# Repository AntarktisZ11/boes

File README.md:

# What is this?

This is Bamses Øhlhäfvarstoppur also called Bøs.

TODO Desc. the rules of häfv.

# Why is this?

TODO

# How to build Bøs (Bamses Øhlhäfvarstoppur)

TODO

## Hardware prerequisites

[List of components](./Hardware.md)

Rough cost estimate: 1000-800kr

<details>
<summary>Pico RGB matrix pinout</summary>
<br>
TODO add pinout

</details>

### Main PCB

[Schematic PDF](./docs/pcb-boes-main/boes-schematic.pdf)

[CSV BoM](./docs/pcb-boes-main/BoM/boes-bom.csv)

[Interactive BoM](./docs/pcb-boes-main/BoM/boes-ibom.html) (Download and view in browser.)

#### Top and bottom view of PCB

### USB-C Power distribution PCB

[Schematic PDF](./docs/pcb-boes-usb-c/boes_usb-c-schematic.pdf)

[CSV BoM](./docs/pcb-boes-usb-c/BoM/boes_usb-c-bom.csv)

[Interactive BoM](./docs/pcb-boes-usb-c/BoM/boes_usb-c-ibom.html) (Download and view in browser.)

#### Top and bottom view of PCB

### Sensor PCB

[Schematic PDF](./docs/pcb-boes-sensor/boes_sensor-schematic.pdf)

[CSV BoM](./docs/pcb-boes-sensor/BoM/boes_sensor-bom.csv)

[Interactive BoM](./docs/pcb-boes-sensor/BoM/boes_sensor-ibom.html) (Download and view in browser.)

#### Top and bottom view of PCB

## Software prerequisites

The following tools and libraries are required to compile and flash the Pico.

- Arduino CLI tool (or Arduino IDE, whatever works)
- [Raspberry Pi Pico Arduino core](https://github.com/earlephilhower/arduino-pico)
- Adafruit and Arduino libraries (see below)

## Linux guide

Install Pico Arduino core (if not already prepared):

```bash
# Initialize arduino-cli
arduino-cli config init

# Add Pico url to additional_urls like this:
additional_urls: [https://github.com/earlephilhower/arduino-pico/releases/download/global/package_rp2040_index.json]

# Update index to download rp2040 config
arduino-cli core update-index

# Download Pico cores
arduino-cli core install rp2040:rp204
```

Install the required libraries:

```bash
# Note: 'arduino-cli lib install <library>' installs <library>
# and all its dependencies.

# Adafruit library required to driver the led matrix.
arduino-cli lib install "Adafruit Protomatter"

# Protothread / simulated threads in software to schedule
# timer, display and button controllers.
arduino-cli lib install "ArduinoThread"
```

## Compiling and uploading binary

After the prerequisites are satisfied you should be able to compile and upload the binary to the Pico.

```bash
# Compile and upload binary.
# (Note: For me <serial> was set to /dev/ttyACM0)
arduino-cli compile -u -p <serial> -b rp2040:rp2040:rpipicow display/display.ino
```

# Future improvements

- Separate code into thread classes (e.g. display and web server handling in their own respective class)
- Config file handling for constants/delays/logo (USB mass storage) when plugging the cable (also allow uploading configs on web server site?)
- HTML/CSS file handling (USB mass storage).. not the crude http response way that is currently implemented

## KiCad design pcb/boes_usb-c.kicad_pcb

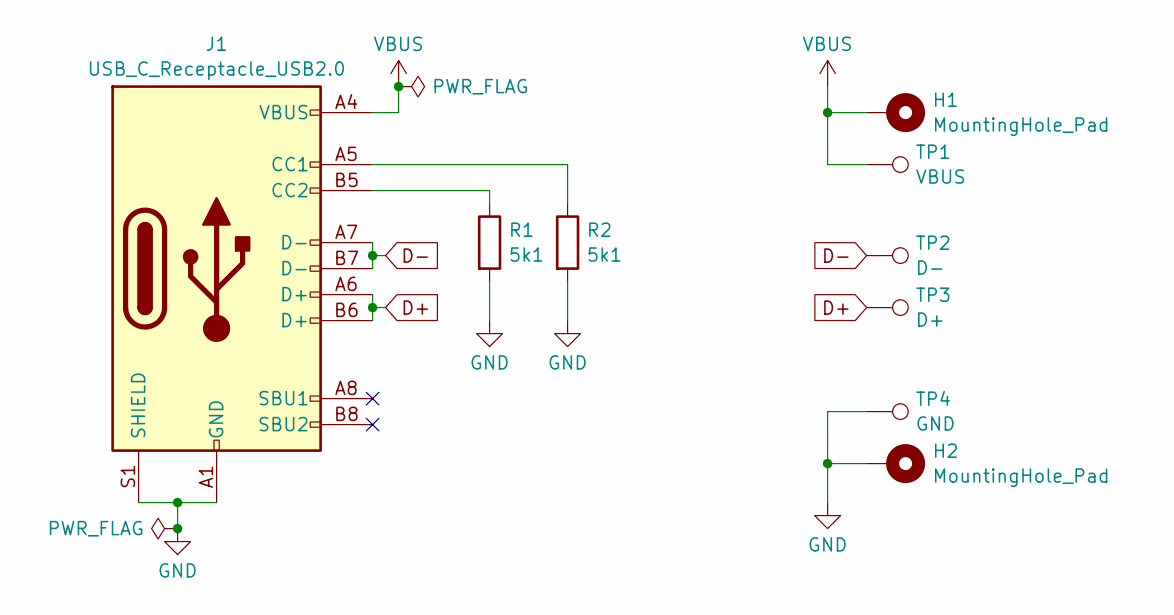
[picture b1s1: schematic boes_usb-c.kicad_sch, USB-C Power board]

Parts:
H1, H2: MountingHole_Pad; MountingHole_3.2mm_M3_Pad_TopOnly
J1: USB_C_Receptacle_USB2.0; USB_C_Receptacle_GCT_USB4105-xx-A_16P_TopMnt_Horizontal
R1, R2: 5k1; R_0603_1608Metric
TP1: VBUS; SolderWire-0.5sqmm_1x01_D0.9mm_OD2.1mm_Relief
TP2: D-; SolderWire-0.1sqmm_1x01_D0.4mm_OD1mm_Relief
TP3: D+; SolderWire-0.1sqmm_1x01_D0.4mm_OD1mm_Relief
TP4: GND; SolderWire-0.5sqmm_1x01_D0.9mm_OD2.1mm_Relief

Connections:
D+: J1.A6 (D+), J1.B6 (D+), TP3.1
D-: J1.A7 (D-), J1.B7 (D-), TP2.1
GND: H2.1, J1.A1 (GND), J1.A12 (GND), J1.B1 (GND), J1.B12 (GND), J1.S1 (SHIELD), R1.2, R2.2, TP4.1
unnamed: J1.A5 (CC1), R2.1
unnamed: J1.B5 (CC2), R1.1
VBUS: H1.1, J1.A4 (VBUS), J1.A9 (VBUS), J1.B4 (VBUS), J1.B9 (VBUS), TP1.1

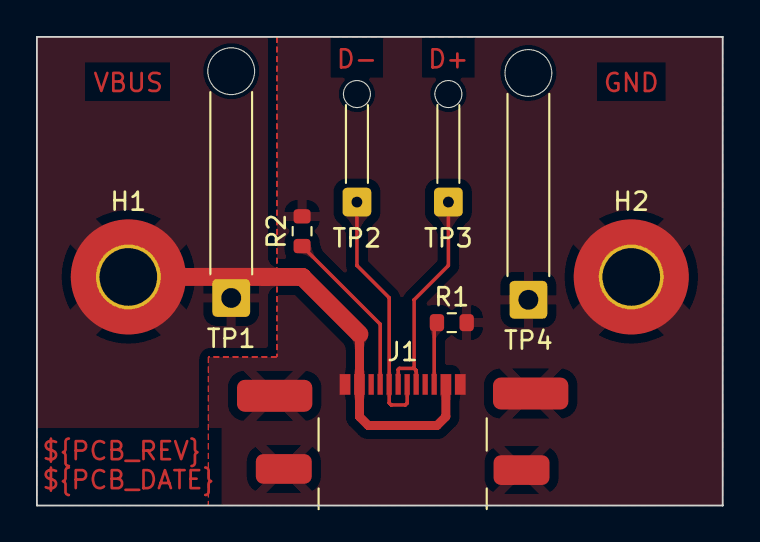
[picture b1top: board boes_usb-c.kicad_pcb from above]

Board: 2 copper layers, 38.1 x 26.0 mm, 9 parts (0 on the bottom side), 6 nets.

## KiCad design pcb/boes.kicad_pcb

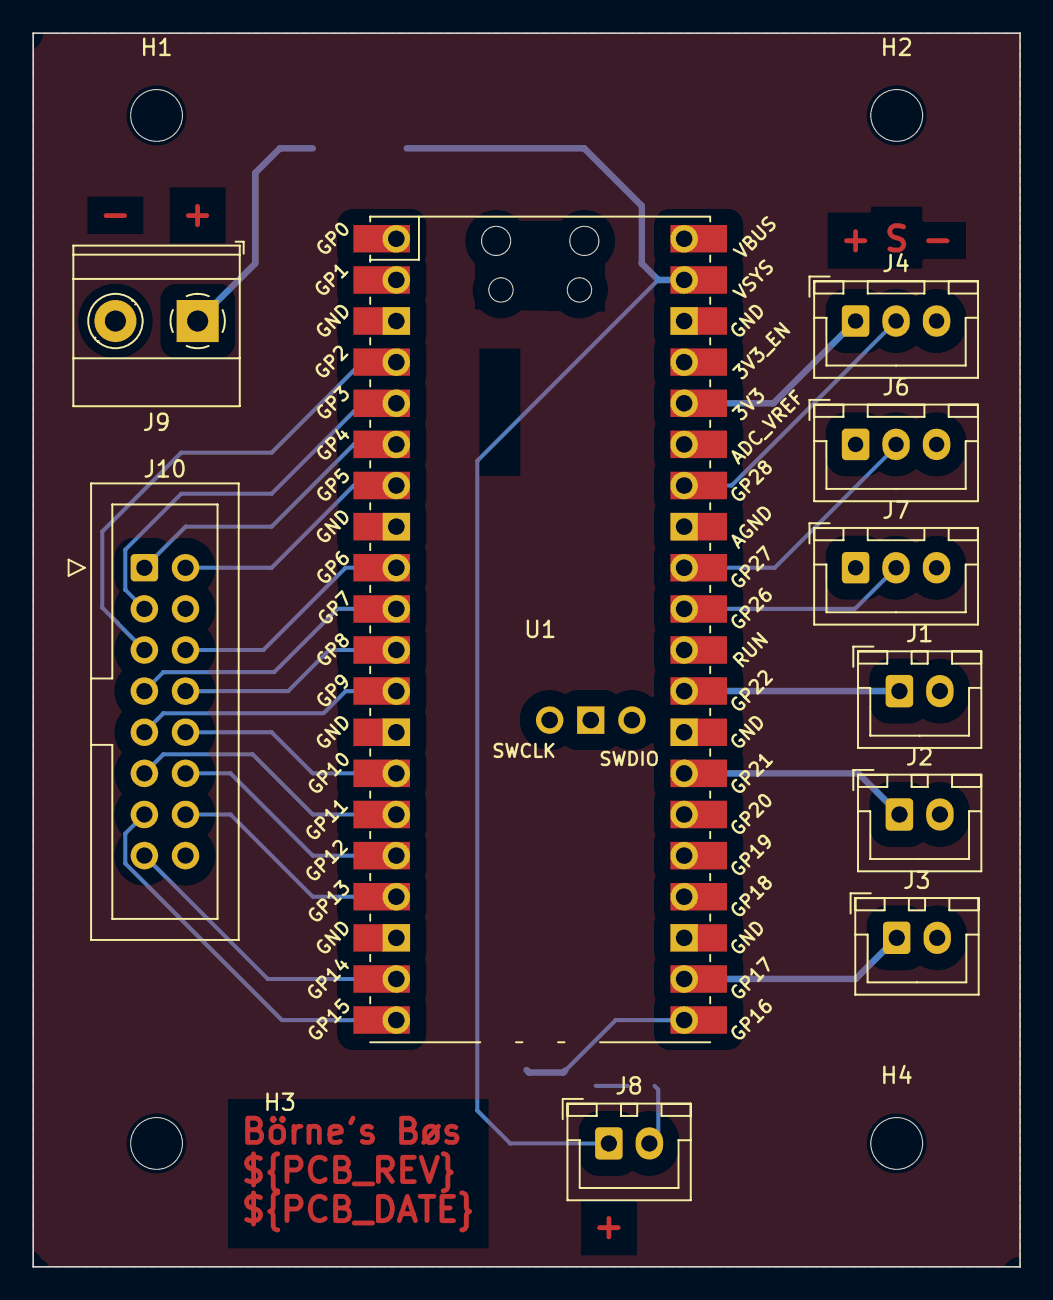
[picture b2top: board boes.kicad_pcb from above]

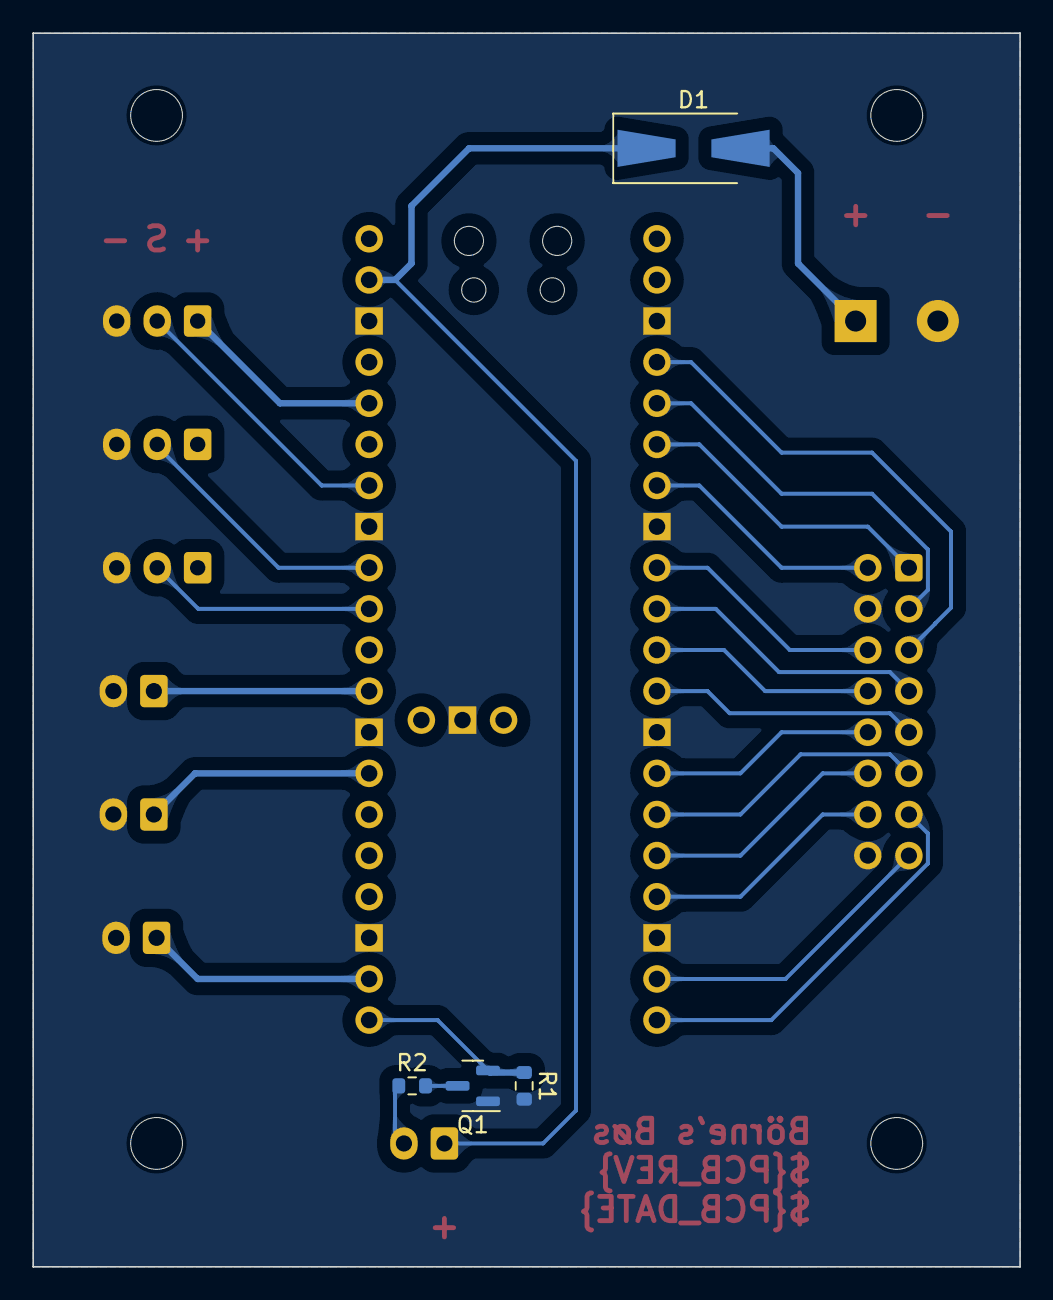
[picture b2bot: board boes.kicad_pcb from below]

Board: 2 copper layers, 61.0 x 76.2 mm, 18 parts (4 on the bottom side), 27 nets.

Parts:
D1: D_Schottky; D_SMA-SMB_Universal_Handsoldering
H1, H2, H3, H4: MountingHole; MountingHole_3.2mm_M3
J1: SW_A; JST_XH_B2B-XH-A_1x02_P2.50mm_Vertical
J2: SW_B; JST_XH_B2B-XH-A_1x02_P2.50mm_Vertical
J3: SW_C; JST_XH_B2B-XH-A_1x02_P2.50mm_Vertical
J4: Pot_J; JST_XH_B3B-XH-A_1x03_P2.50mm_Vertical
J6: Sens_J; JST_XH_B3B-XH-A_1x03_P2.50mm_Vertical
J7: Sens_P; JST_XH_B3B-XH-A_1x03_P2.50mm_Vertical
J8: Buzzer; JST_XH_B2B-XH-A_1x02_P2.50mm_Vertical
J9: +5V External; TerminalBlock_Phoenix_MKDS-1,5-2-5.08_1x02_P5.08mm_Horizont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
J10: HUB75 Display ctrl; IDC-Header_2x08_P2.54mm_Vertical
Q1: 2N7000; SOT-23
R1: 10k; R_0603_1608Metric
R2: R; R_0603_1608Metric
U1: PicoW; RPi_PicoW_SMD_TH

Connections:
+3V3: J4.1, J6.1, J7.1, U1.36 (3V3)
A: J10.9, U1.12 (GPIO9)
B: J10.10, U1.14 (GPIO10)
B1: J10.3, U1.5 (GPIO3)
B2: J10.7, U1.10 (GPIO7)
Buzzer: Q1.2 (G), R1.1, U1.21 (GPIO16)
C: J10.11, U1.15 (GPIO11)
CLK: J10.13, U1.20 (GPIO15)
D: J10.12, U1.16 (GPIO12)
E: J10.8, U1.11 (GPIO8)
G1: J10.2, U1.7 (GPIO5)
G2: J10.6, U1.9 (GPIO6)
GND: J1.2, J2.2, J3.2, J4.3, J6.3, J7.3, J9.2, J10.4, J10.16, Q1.1 (S), R1.2, U1.3 (GND), U1.8 (GND), U1.13 (GND), U1.18 (GND), U1.23 (GND), U1.28 (GND), U1.33 (AGND), U1.38 (GND), U1.42 (GND)
Latch: J10.14, U1.17 (GPIO13)
unnamed: D1.2 (A), J9.1
unnamed: J8.2, R2.1
unnamed: Q1.3 (D), R2.2
OE: J10.15, U1.19 (GPIO14)
Pot: J4.2, U1.34 (GPIO28_ADC2)
R1: J10.1, U1.6 (GPIO4)
R2: J10.5, U1.4 (GPIO2)
Reset: J3.1, U1.22 (GPIO17)
Sens_J: J6.2, U1.32 (GPIO27_ADC1)
Sens_P: J7.2, U1.31 (GPIO26_ADC0)
Start: J1.1, U1.29 (GPIO22)
Stop: J2.1, U1.27 (GPIO21)
VCC: D1.1 (K), J8.1, U1.39 (VSYS)

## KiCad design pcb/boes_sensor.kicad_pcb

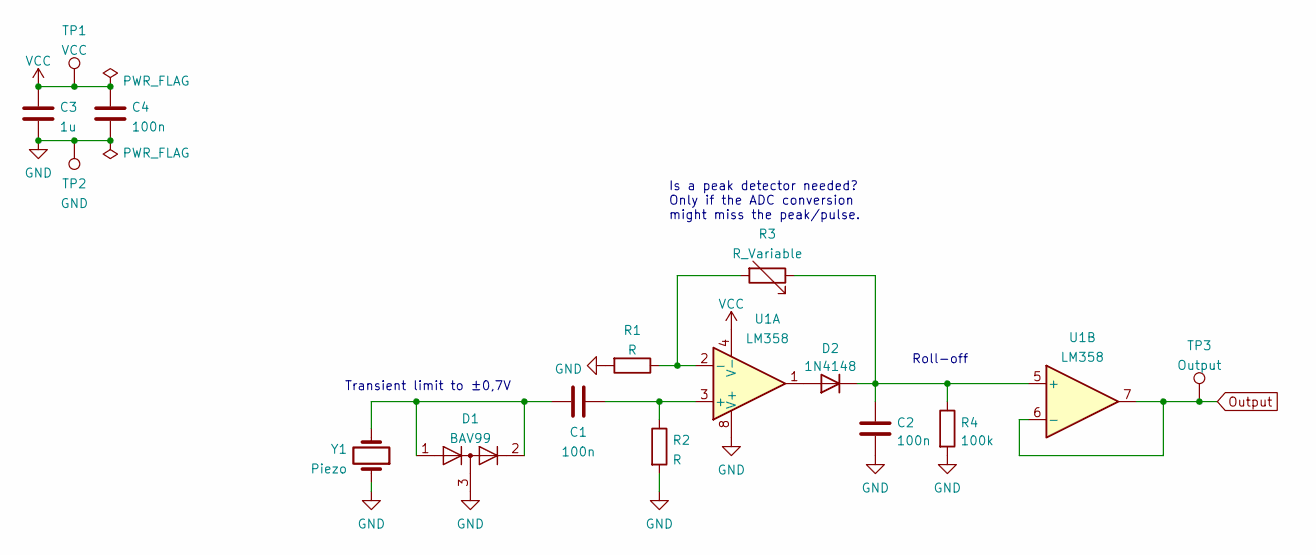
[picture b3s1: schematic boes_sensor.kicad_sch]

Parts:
C1, C2, C4: 100n; C_0603_1608Metric
C3: 1u; C_0603_1608Metric
D1: BAV99; SOT-23
D2: 1N4148; D_MiniMELF
R1, R2: R; R_0603_1608Metric
R3: R_Variable; R_0603_1608Metric
R4: 100k; R_0603_1608Metric
TP1: VCC; SolderWire-0.25sqmm_1x01_D0.65mm_OD1.7mm_Relief
TP2: GND; SolderWire-0.25sqmm_1x01_D0.65mm_OD1.7mm_Relief
TP3: Output; SolderWire-0.25sqmm_1x01_D0.65mm_OD1.7mm_Relief
U1: LM358; SOIC-8_3.9x4.9mm_P1.27mm
Y1: Piezo; SolderWire-0.1sqmm_1x02_P3.6mm_D0.4mm_OD1mm_Relief

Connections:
GND: C2.2, C3.2, C4.2, D1.3 (K), R1.2, R2.2, R4.2, TP2.1, U1.8 (V+), Y1.1
unnamed: C1.1, D1.1 (K), D1.2 (A), Y1.2
unnamed: C1.2, R2.1, U1.3 (+)
unnamed: C2.1, D2.1 (K), R3.1, R4.1, U1.5 (+)
unnamed: D2.2 (A), U1.1
unnamed: R1.1, R3.2, U1.2 (-)
Output: TP3.1, U1.6 (-), U1.7
VCC: C3.1, C4.1, TP1.1, U1.4 (V-)

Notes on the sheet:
Transient limit to ±0,7V
Is a peak detector needed? Only if the ADC conversion might miss the peak/pulse.
Roll-off

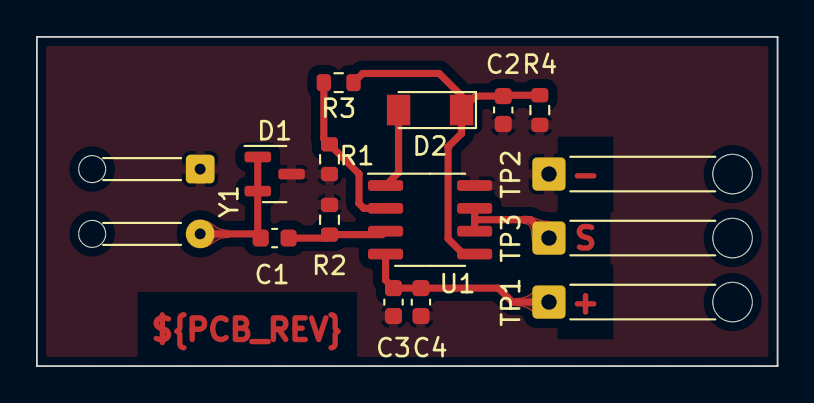
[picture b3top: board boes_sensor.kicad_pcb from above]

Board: 2 copper layers, 41.1 x 18.3 mm, 15 parts (0 on the bottom side), 8 nets.

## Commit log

2023-07-22 Add TODO and clarification comments
2023-07-22 Change folder structure
2023-07-22 Initial hardware commit
2023-07-22 Add KiCad library submodule
2023-08-05 Separate main board from sensor boards
2023-08-09 Almost finished main board
2023-08-13 Update .kibot submodule
2023-08-13 Add full PCB documentation dispatch workflow
2023-08-13 Add automatic PCB docs update workflow
2023-08-13 Main PCB ready for final tweaks
2023-08-13 Add finished sensor PCB
2023-08-13 Update pcb_change.yaml to trigger on master branch
2023-08-13 Only trigger build workflow on path 'code/**'
2023-08-13 Fix 'not a git repository' error on upload
2023-08-13 Update PCB Documentation
2023-08-13 Add PCB section to README
2023-08-13 Use teardrop pads for sensor PCB
2023-08-13 Fix auto-commit not running if event was push
2023-08-13 Add decoupling to sensor VCC rail
2023-08-16 Slim main PCB
2023-08-18 Remove need for Pico W
2023-08-23 Fix SCH_REV substitution
2023-08-24 Revert "Remove need for Pico W"
    This reverts commits:
    d2ab96132ced680a2e2da26c64405593ad7260a6
    dff21f3cf701d05c1464d47412e9ae388ae68376
2023-08-28 Upgrade to KiCad 7
2023-08-28 Add teardrops to main PCB
2023-08-29 Repurpose screw terminal as input
2023-08-29 Add teardrops to last change
2023-08-29 Add USB-C power board
2023-08-29 Add USB-C Power distribution PCB to README
2023-08-29 Improve VBUS filled zone
2023-08-30 Improve strain relief
2023-09-09 Update pin assignment to match PCB
2023-09-10 Change display rotation
2023-09-11 Change splash screen
2023-09-11 Fix splash centering
